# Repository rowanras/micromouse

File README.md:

# micromouse2019
A micromouse for the IEEE micromouse competetion. It uses a custom board with an stm32f405, three time of flight distance sensors, two pololu geared motors w/ encoders, and a drv8848 motor controller.

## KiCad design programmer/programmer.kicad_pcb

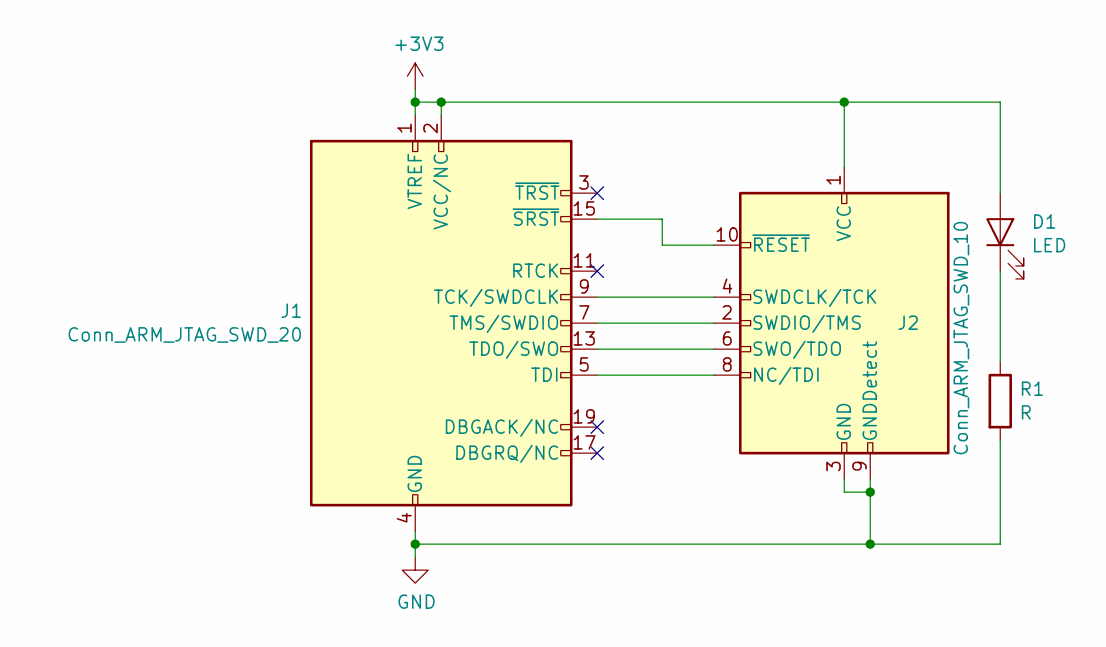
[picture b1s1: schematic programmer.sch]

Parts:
D1: LED; LED_0603_1608Metric
J1: Conn_ARM_JTAG_SWD_20; PinHeader_2x10_P2.54mm_Vertical
J2: Conn_ARM_JTAG_SWD_10; PinHeader_2x05_P1.27mm_Vertical_SMD
R1: R; R_0603_1608Metric

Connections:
+3V3: D1.2 (A), J1.1 (VTREF), J1.2 (VCC/NC), J2.1 (VCC)
GND: J1.4 (GND), J1.6 (GND), J1.8 (GND), J1.10 (GND), J1.12 (GND), J1.14 (GND), J1.16 (GND), J1.18 (GND), J1.20 (GND), J2.3 (GND), J2.5 (GND), J2.9 (GNDDetect), R1.2
unnamed: D1.1 (K), R1.1
unnamed: J1.5 (TDI), J2.8 (NC/TDI)
unnamed: J1.7 (TMS/SWDIO), J2.2 (SWDIO/TMS)
unnamed: J1.9 (TCK/SWDCLK), J2.4 (SWDCLK/TCK)
unnamed: J1.13 (TDO/SWO), J2.6 (SWO/TDO)
unnamed: J1.15 (~SRST~), J2.10 (~RESET~)

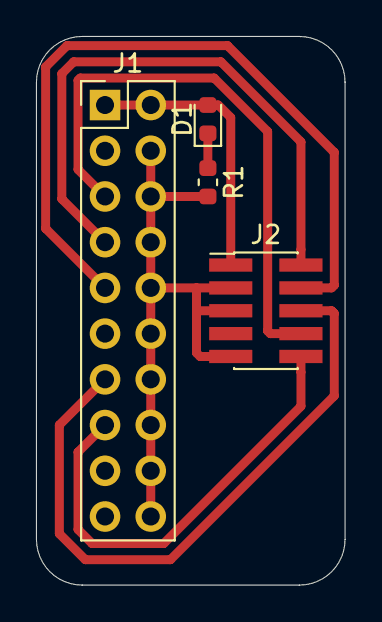
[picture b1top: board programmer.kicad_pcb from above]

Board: 2 copper layers, 17.1 x 30.5 mm, 4 parts (0 on the bottom side), 8 nets.

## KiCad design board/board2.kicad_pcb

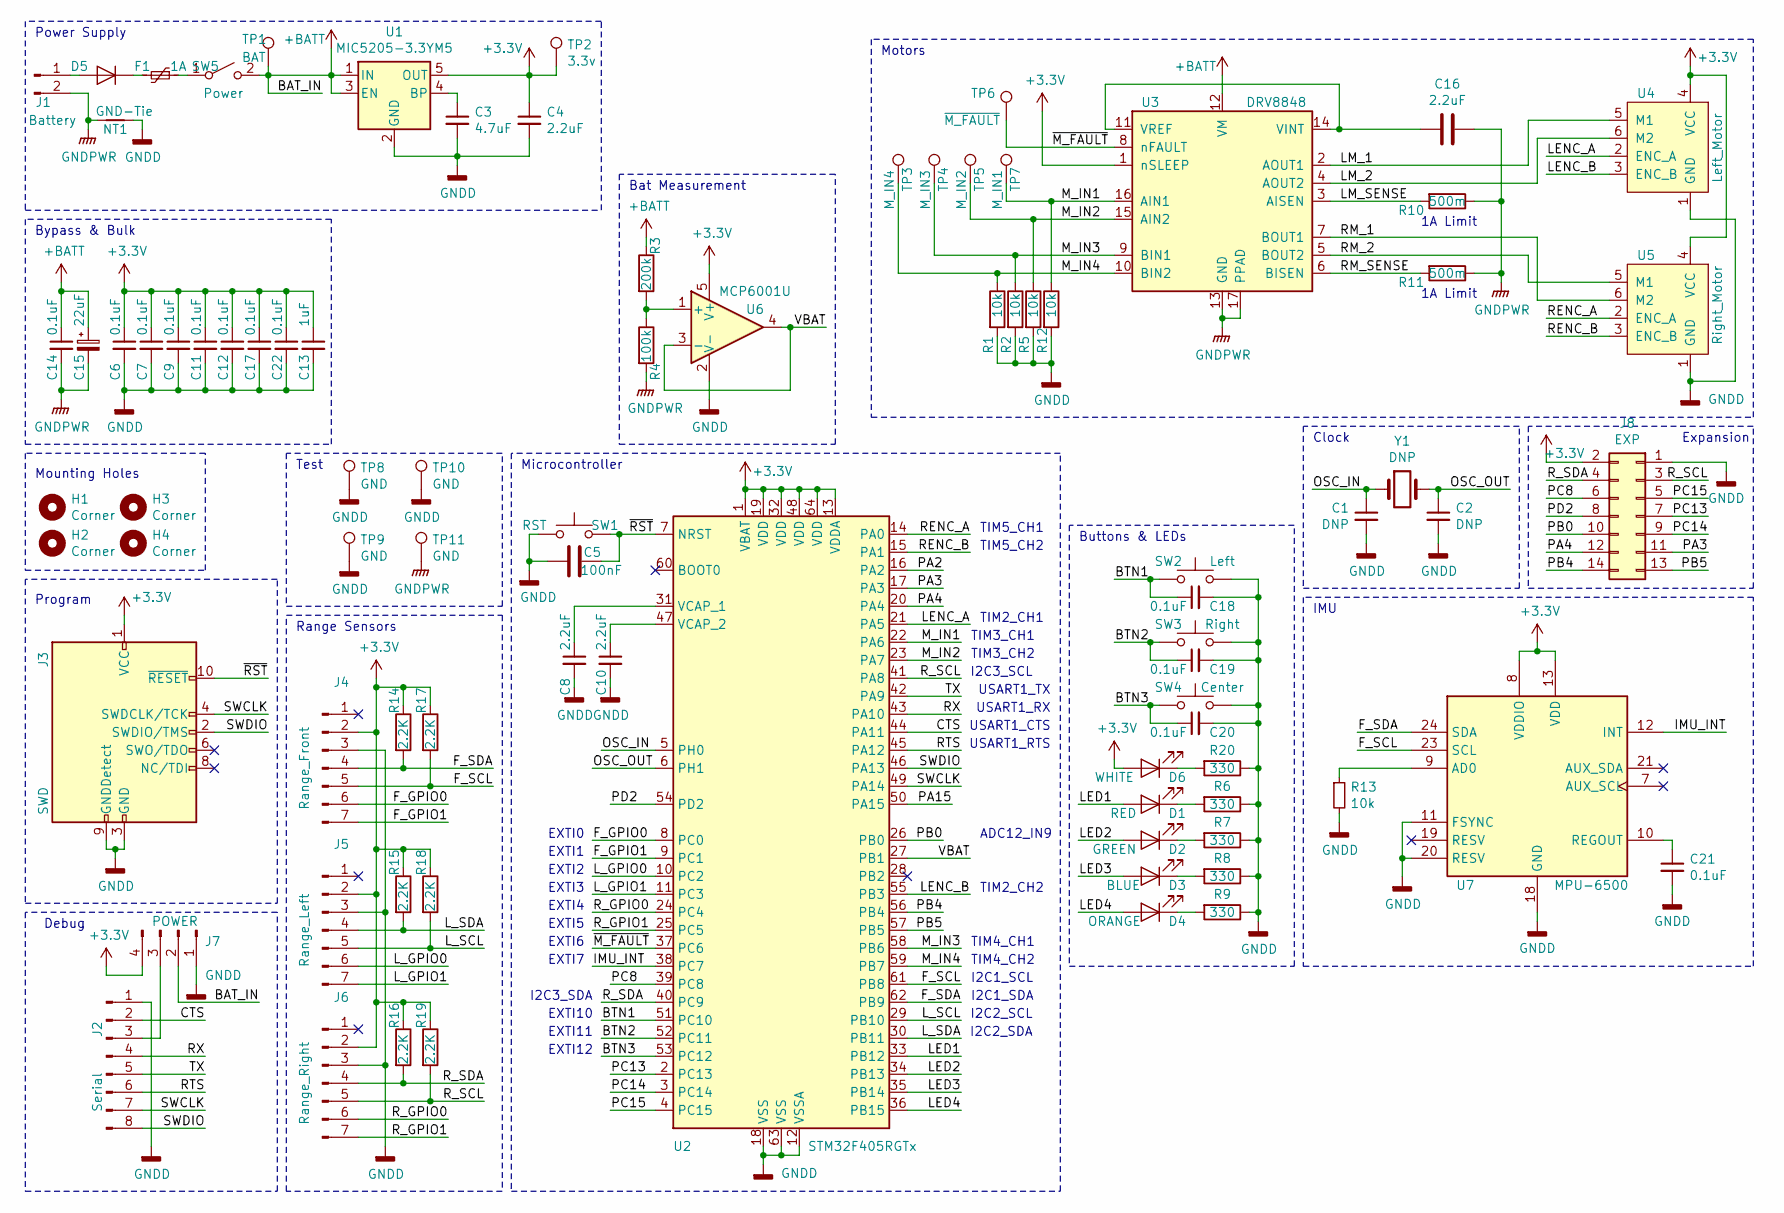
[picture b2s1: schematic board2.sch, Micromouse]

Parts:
C1, C2: DNP; C_0603_1608Metric
C3: 4.7uF; C_0603_1608Metric
C4, C8, C10, C16: 2.2uF; C_0603_1608Metric
C5: 100nF; C_0603_1608Metric
C6, C7, C9, C11, C12, C14, C17, C18, C19, C20, C21, C22: 0.1uF; C_0603_1608Metric
C13: 1uF; C_0603_1608Metric
C15: 22uF; CP_Elec_4x4.5
D1: RED; LED_0603_1608Metric
D2: GREEN; LED_0603_1608Metric
D3: BLUE; LED_0603_1608Metric
D4: ORANGE; LED_0603_1608Metric
D5: DB2441700L; SC-110A-2
D6: WHITE; LED_0603_1608Metric
F1: 1A; Littlefuse_154
H1, H2, H3, H4: Corner; MountingHole_2.2mm_M2
J1: Battery; PinHeader_1x02_P2.54mm_Horizontal
J2: Serial; PinHeader_1x08_P2.54mm_Vertical_SMD_Pin1Left
J3: SWD; PinHeader_2x05_P1.27mm_Vertical_SMD
J4: Range_Front; PinSocket_1x07_P2.54mm_Vertical
J5: Range_Left; PinSocket_1x07_P2.54mm_Vertical
J6: Range_Right; PinSocket_1x07_P2.54mm_Vertical
J7: POWER; PinHeader_1x04_P2.54mm_Vertical_SMD_Pin1Left
J8: EXP; PinHeader_2x07_P2.00mm_Vertical_SMD
NT1: GND-Tie; NetTie-2_SMD_Pad0.5mm
R1, R2, R5, R12, R13: 10k; R_0603_1608Metric
R3: 200k; R_0603_1608Metric
R4: 100k; R_0603_1608Metric
R6, R7, R8, R9, R20: 330; R_0603_1608Metric
R10, R11: 500m; R_1210_3225Metric
R14, R15, R16, R17, R18, R19: 2.2K; R_0603_1608Metric
SW1: RST; SW_SPST_PTS810
SW2: Left; SW_SPST_PTS810
SW3: Right; SW_SPST_PTS810
SW4: Center; SW_SPST_PTS810
SW5: Power; PinHeader_2x01_P2.54mm_Vertical_SMD
TP1: BAT; TestPoint_Pad_1.8x1.0mm
TP2: 3.3v; TestPoint_Pad_1.8x1.0mm
TP3: M_IN4; TestPoint_Pad_1.8x1.0mm
TP4: M_IN3; TestPoint_Pad_1.8x1.0mm
TP5: M_IN2; TestPoint_Pad_1.8x1.0mm
TP6: ~M_FAULT; TestPoint_Pad_1.8x1.0mm
TP7: M_IN1; TestPoint_Pad_1.8x1.0mm
TP8, TP9, TP10, TP11: GND; TestPoint_Pad_1.8x1.0mm
U1: MIC5205-3.3YM5; SOT-23-5
U2: STM32F405RGTx; LQFP-64_10x10mm_P0.5mm
U3: DRV8848; TSSOP-16_4.4x5mm_P0.65mm
U4: Left_Motor; Molex_PicoBlade_53261-0671_1x06-1MP_P1.25mm_Horizontal
U5: Right_Motor; Molex_PicoBlade_53261-0671_1x06-1MP_P1.25mm_Horizontal
U6: MCP6001U; SOT-23-5
U7: MPU-6500; InvenSense_QFN-24_3x3mm_P0.4mm
Y1: DNP; Crystal_SMD_0603-2Pin_6.0x3.5mm

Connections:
+3V3: C4.1, C6.1, C7.1, C9.1, C11.1, C12.1, C13.1, C17.1, C22.1, D6.2 (A), J3.1 (VCC), J4.2, J5.2, J6.2, J7.4, J8.2, R14.1, R15.1, R16.1, R17.1, R18.1, R19.1, TP2.1, U1.5 (OUT), U2.1 (VBAT), U2.13 (VDDA), U2.19 (VDD), U2.32 (VDD), U2.48 (VDD), U2.64 (VDD), U3.1 (nSLEEP), U4.4 (VCC), U5.4 (VCC), U6.5 (V+), U7.8 (VDDIO), U7.13 (VDD)
+BATT: C14.1, C15.1, J7.2, R3.1, SW5.2 (B), TP1.1, U1.1 (IN), U1.3 (EN), U3.12 (VM)
/BTN1: C18.1, SW2.1, U2.51 (PC10)
/BTN2: C19.1, SW3.1, U2.52 (PC11)
/BTN3: C20.1, SW4.1, U2.53 (PC12)
/CTS: J2.2, U2.44 (PA11)
/F_GPIO0: J4.6, U2.8 (PC0)
/F_GPIO1: J4.7, U2.9 (PC1)
/F_SCL: J4.5, R17.2, U2.61 (PB8), U7.23 (SCL)
/F_SDA: J4.4, R14.2, U2.62 (PB9), U7.24 (SDA)
/IMU_INT: U2.38 (PC7), U7.12 (INT)
/LED1: D1.2 (A), U2.33 (PB12)
/LED2: D2.2 (A), U2.34 (PB13)
/LED3: D3.2 (A), U2.35 (PB14)
/LED4: D4.2 (A), U2.36 (PB15)
/LENC_A: U2.21 (PA5), U4.2 (ENC_A)
/LENC_B: U2.55 (PB3), U4.3 (ENC_B)
/LM_1: U3.2 (AOUT1), U4.5 (M1)
/LM_2: U3.4 (AOUT2), U4.6 (M2)
/LM_SENSE: R10.2, U3.3 (AISEN)
/L_GPIO0: J5.6, U2.10 (PC2)
/L_GPIO1: J5.7, U2.11 (PC3)
/L_SCL: J5.5, R18.2, U2.29 (PB10)
/L_SDA: J5.4, R15.2, U2.30 (PB11)
/M_IN1: R12.1, TP7.1, U2.22 (PA6), U3.16 (AIN1)
/M_IN2: R5.1, TP5.1, U2.23 (PA7), U3.15 (AIN2)
/M_IN3: R2.1, TP4.1, U2.58 (PB6), U3.9 (BIN1)
/M_IN4: R1.1, TP3.1, U2.59 (PB7), U3.10 (BIN2)
/OSC_IN: C1.1, U2.5 (PH0), Y1.1
/OSC_OUT: C2.1, U2.6 (PH1), Y1.2
/PA3: J8.11, U2.17 (PA3)
/PA4: J8.12, U2.20 (PA4)
/PB0: J8.10, U2.26 (PB0)
/PB4: J8.14, U2.56 (PB4)
/PB5: J8.13, U2.57 (PB5)
/PC8: J8.6, U2.39 (PC8)
/PC13: J8.7, U2.2 (PC13)
/PC14: J8.9, U2.3 (PC14)
/PC15: J8.5, U2.4 (PC15)
/PD2: J8.8, U2.54 (PD2)
/RENC_A: U2.14 (PA0), U5.2 (ENC_A)
/RENC_B: U2.15 (PA1), U5.3 (ENC_B)
/RM_1: U3.7 (BOUT1), U5.6 (M2)
/RM_2: U3.5 (BOUT2), U5.5 (M1)
/RM_SENSE: R11.2, U3.6 (BISEN)
/RTS: J2.6, U2.45 (PA12)
/RX: J2.4, U2.43 (PA10)
/R_GPIO0: J6.6, U2.24 (PC4)
/R_GPIO1: J6.7, U2.25 (PC5)
/R_SCL: J6.5, J8.3, R19.2, U2.41 (PA8)
/R_SDA: J6.4, J8.4, R16.2, U2.40 (PC9)
/SWCLK: J2.7, J3.4 (SWDCLK/TCK), U2.49 (PA14)
/SWDIO: J2.8, J3.2 (SWDIO/TMS), U2.46 (PA13)
/TX: J2.5, U2.42 (PA9)
/VBAT: U2.27 (PB1), U6.3 (-), U6.4
/~M_FAULT: TP6.1, U2.37 (PC6), U3.8 (nFAULT)
/~RST: C5.1, J3.10 (~RESET~), SW1.2, U2.7 (NRST)
GNDD: C1.2, C2.2, C3.2, C4.2, C5.2, C6.2, C7.2, C8.2, C9.2, C10.2, C11.2, C12.2, C13.2, C17.2, C18.2, C19.2, C20.2, C21.2, C22.2, J2.1, J3.3 (GND), J3.5 (GND), J3.9 (GNDDetect), J4.3, J5.3, J6.3, J7.1, J8.1, NT1.2, R1.2, R2.2, R5.2, R6.1, R7.1, R8.1, R9.1, R12.2, R13.2, R20.1, SW1.1, SW2.2, SW3.2, SW4.2, TP8.1, TP9.1, TP10.1, U1.2 (GND), U2.12 (VSSA), U2.18 (VSS), U2.63 (VSS), U4.1 (GND), U5.1 (GND), U6.2 (V-), U7.11 (FSYNC), U7.18 (GND), U7.20 (RESV)
GNDPWR: C14.2, C15.2, C16.1, J1.2, NT1.1, R4.2, R10.1, R11.1, TP11.1, U3.13 (GND), U3.17 (PPAD)
unnamed: C3.1, U1.4 (BP)
unnamed: C8.1, U2.31 (VCAP_1)
unnamed: C10.1, U2.47 (VCAP_2)
unnamed: C16.2, U3.11 (VREF), U3.14 (VINT)
unnamed: C21.1, U7.10 (REGOUT)
unnamed: D1.1 (K), R6.2
unnamed: D2.1 (K), R7.2
unnamed: D3.1 (K), R8.2
unnamed: D4.1 (K), R9.2
unnamed: D5.1 (K), F1.2
unnamed: D5.2 (A), J1.1
unnamed: D6.1 (K), R20.2
unnamed: F1.1, SW5.1 (A)
unnamed: J2.3, J7.3
unnamed: R3.2, R4.1, U6.1 (+)
unnamed: R13.1, U7.9 (AD0)

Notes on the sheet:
TIM3_CH1
TIM3_CH2
TIM4_CH1
TIM4_CH2
TIM5_CH1
TIM5_CH2
TIM2_CH1
TIM2_CH2
I2C1_SCL
I2C1_SDA
I2C2_SCL
I2C2_SDA
I2C3_SCL
I2C3_SDA
EXTI0
EXTI1
EXTI2
EXTI3
EXTI4
EXTI5
EXTI6
USART1_TX
USART1_RX
USART1_CTS
USART1_RTS
EXTI10
EXTI11
EXTI12
ADC12_IN9
EXTI7
Range Sensors
IMU
Microcontroller
Buttons & LEDs
Expansion
Clock
Program
Debug
Test
Power Supply

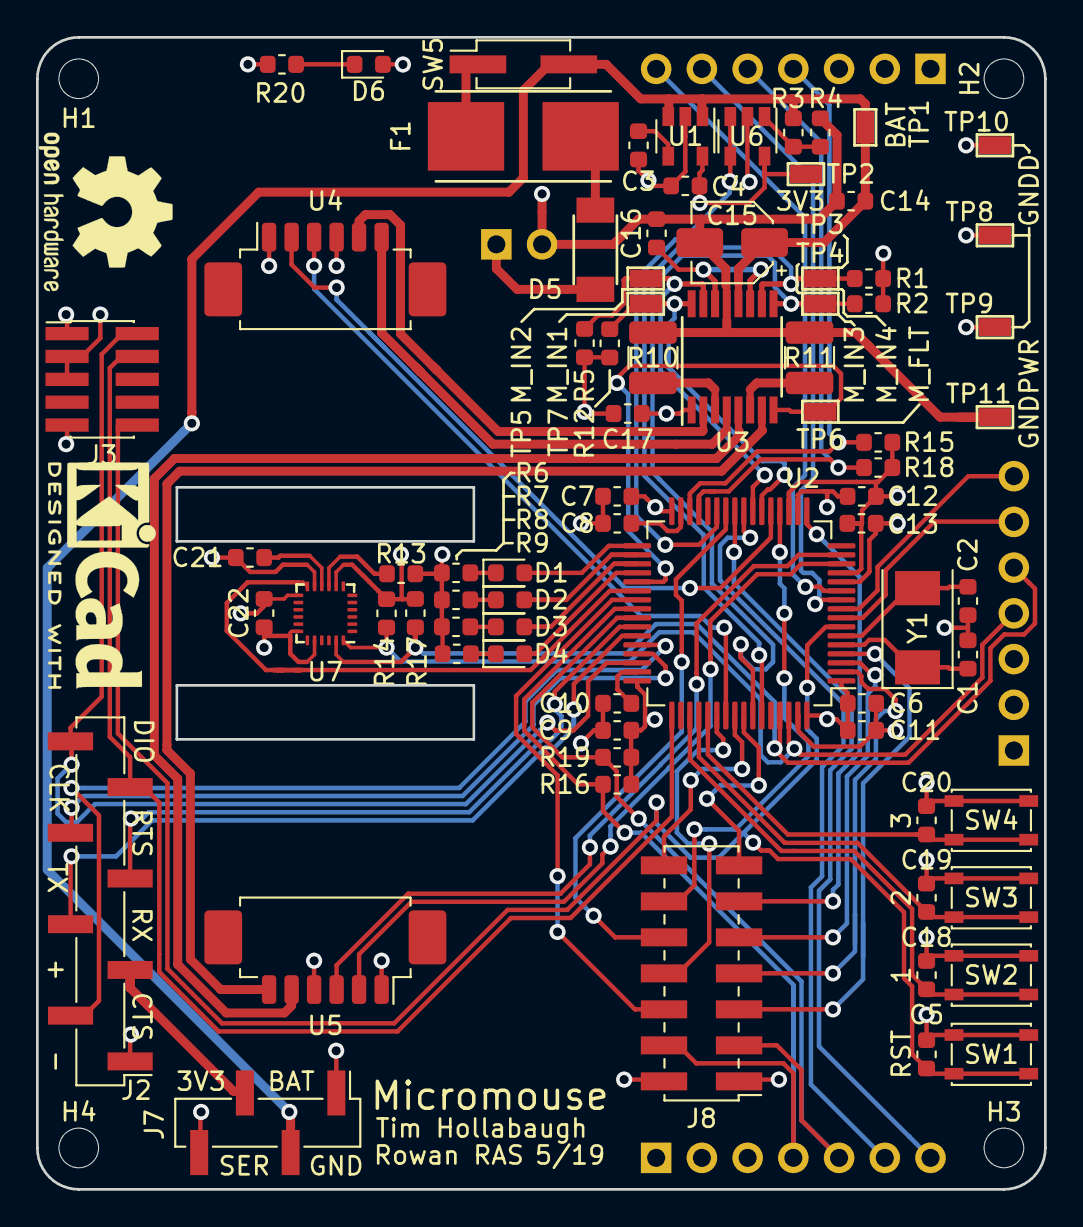
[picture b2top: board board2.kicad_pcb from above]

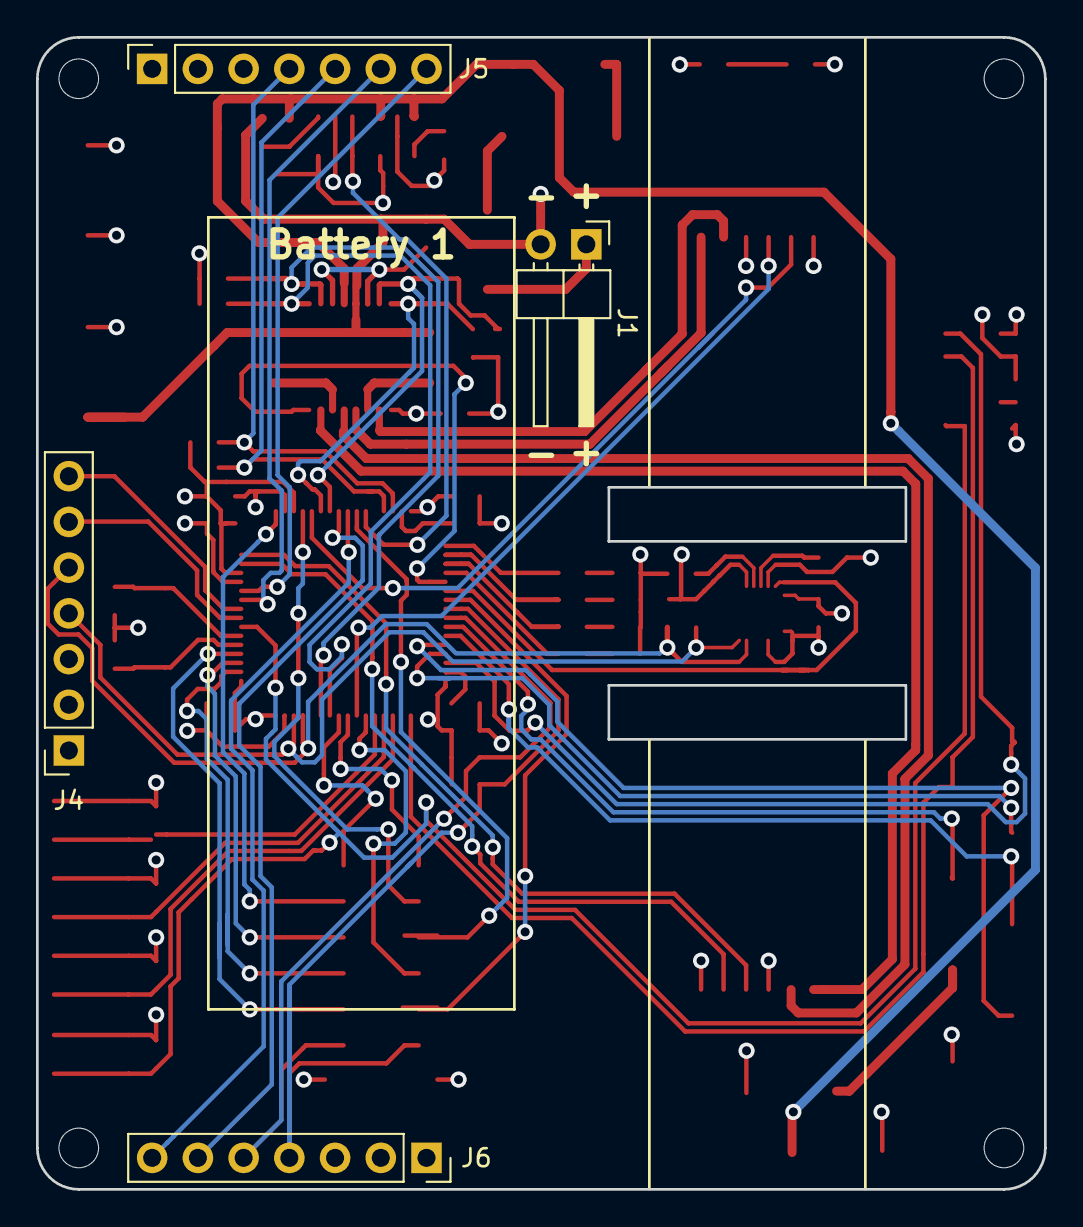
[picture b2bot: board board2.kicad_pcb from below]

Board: 4 copper layers, 56.0 x 64.0 mm, 86 parts (4 on the bottom side), 75 nets.

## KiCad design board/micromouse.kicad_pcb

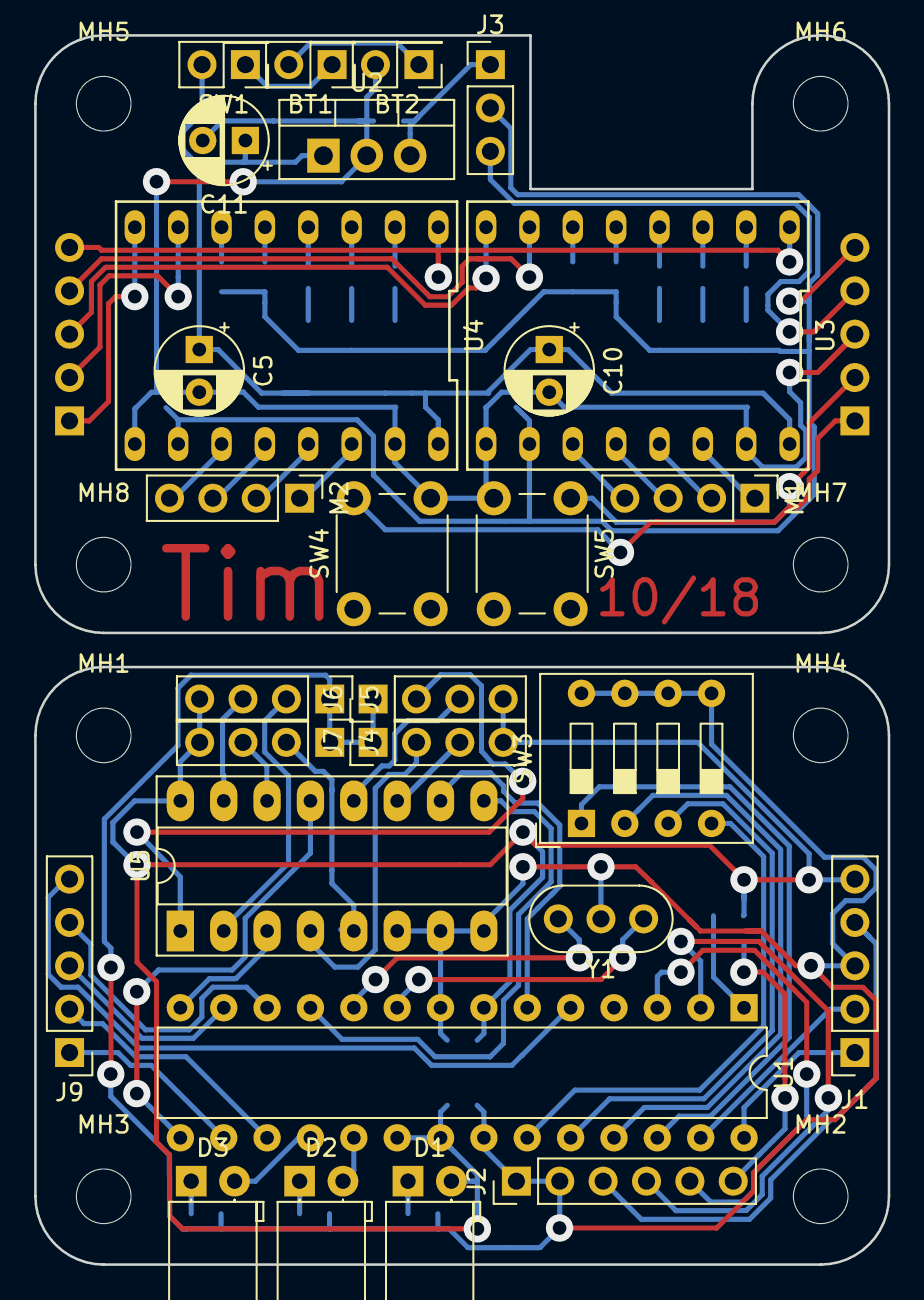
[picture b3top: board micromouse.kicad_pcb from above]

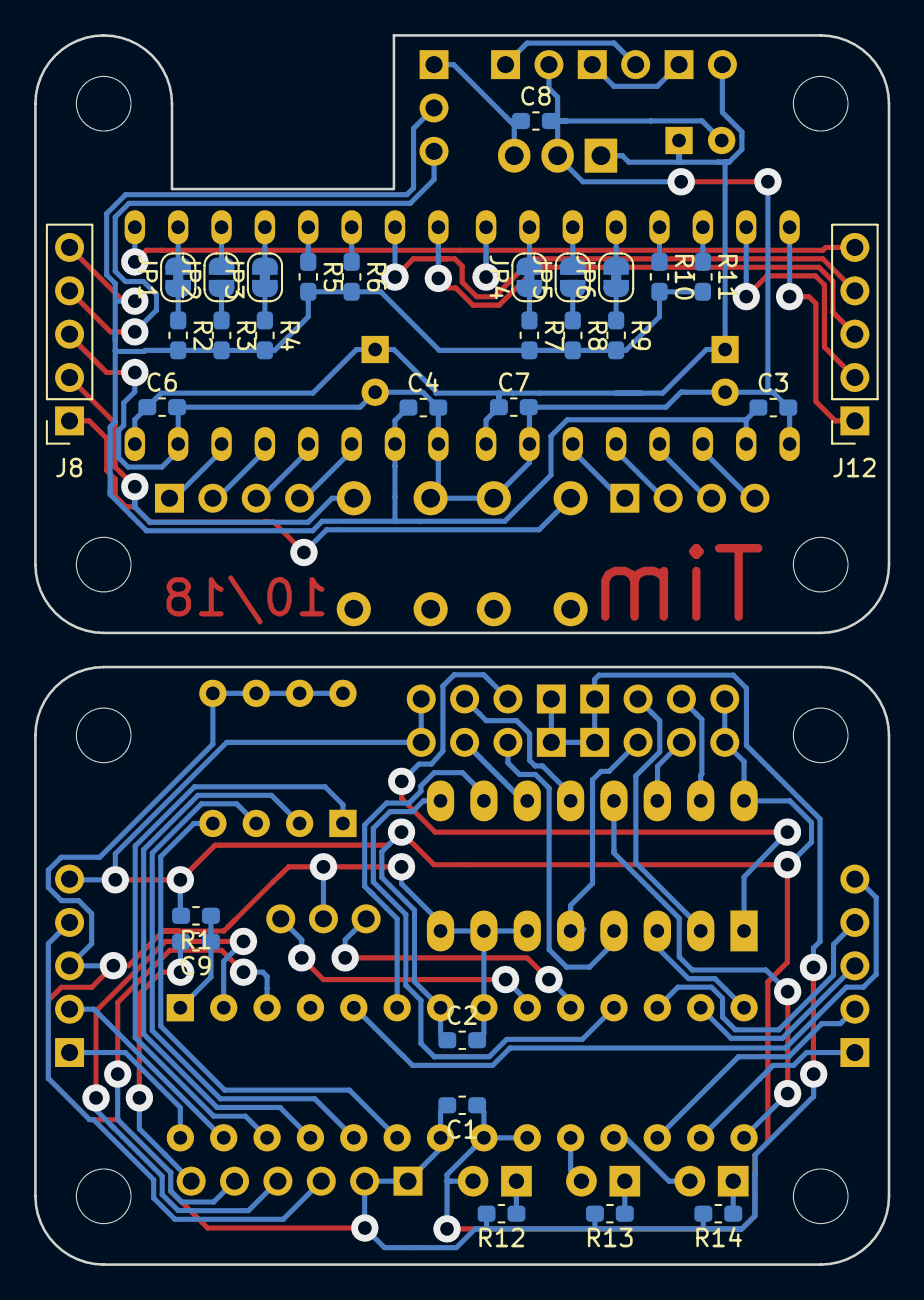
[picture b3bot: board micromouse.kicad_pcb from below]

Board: 2 copper layers, 50.0 x 72.0 mm, 66 parts (30 on the bottom side), 75 nets.

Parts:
BT1, BT2: 3x AA; PinHeader_2x01_P2.54mm_Vertical
C1, C2, C3, C4, C6, C7, C9: 0.1uF; C_0603_1608Metric_Pad1.05x0.95mm_HandSolder
C5: 0.33uf; CP_Radial_D5.0mm_P2.50mm
C8: 0.1uf; C_0603_1608Metric_Pad1.05x0.95mm_HandSolder
C10, C11: CP; CP_Radial_D5.0mm_P2.50mm
D1, D2, D3: LED; LED_D5.0mm_Horizontal_O1.27mm_Z3.0mm
J1: PowerBtnLower; PinSocket_1x05_P2.54mm_Vertical
J2: SERIAL; PinHeader_1x06_P2.54mm_Vertical
J3: PWR_SEL; PinHeader_1x03_P2.54mm_Vertical
J4: Front Sense; PinHeader_1x04_P2.54mm_Vertical
J5: Left Sense; PinHeader_1x04_P2.54mm_Vertical
J6: Right Sense; PinHeader_1x04_P2.54mm_Vertical
J7: Back Sense; PinHeader_1x04_P2.54mm_Vertical
J8: PowerBtnUpper; PinSocket_1x05_P2.54mm_Vertical
J9: MotorsLower; PinHeader_1x05_P2.54mm_Vertical
J12: MotorsUpper; PinSocket_1x05_P2.54mm_Vertical
JP1, JP4: MS1; SolderJumper-2_P1.3mm_Bridged_RoundedPad1.0x1.5mm
JP2, JP5: MS2; SolderJumper-2_P1.3mm_Open_RoundedPad1.0x1.5mm
JP3, JP6: MS3; SolderJumper-2_P1.3mm_Bridged_RoundedPad1.0x1.5mm
M1: Left Motor; PinHeader_1x04_P2.54mm_Vertical
M2: Right Motor; PinHeader_1x04_P2.54mm_Vertical
MH1, MH2, MH3, MH4, MH5, MH6, MH7, MH8: MountingHole; MountingHole_3.2mm_M3
R1, R2, R3, R4, R5, R6, R7, R8, R9, R10, R11: 1K; R_0603_1608Metric_Pad1.05x0.95mm_HandSolder
R12, R13, R14: 470; R_0603_1608Metric_Pad1.05x0.95mm_HandSolder
SW1: SW_SPST; PinHeader_2x01_P2.54mm_Vertical
SW3: SW_DIP_x04; SW_DIP_SPSTx04_Slide_9.78x12.34mm_W7.62mm_P2.54mm
SW4, SW5: SW_Push; SW_PUSH_6mm
U1: ATmega328P-PU; DIP-28_W7.62mm
U2: L7805; TO-220-3_Vertical
U3, U4: drv8825; DIP-16_500_ELL
U5: CD4052B; DIP-16_W7.62mm_Socket_LongPads
Y1: 16MHz; Resonator-3Pin_W8.0mm_H3.5mm

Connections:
+5V: C3.1, C4.1, J3.2, J8.5, R2.2, R3.2, R4.2, R5.2, R6.2, R7.2, R8.2, R9.2, R10.2, R11.2, U3.10, U4.10
+5VD: C1.1, C2.1, D1.2, J1.5, J4.4, J5.4, J6.4, J7.4, R1.2, U1.7, U1.20, U1.21, U5.16
+BATT: C5.1, C6.1, C7.1, C10.1, C11.1, SW1.2, U2.1, U3.16, U4.16
/BACK_ECHO: J7.2, U5.4
/BACK_TRIG: J7.3, U5.11
/BTN1: J1.1, U1.28
/BTN1_T: J8.1, SW4.1
/BTN2: J1.2, U1.27
/BTN2_T: J8.2, SW5.1
/FRONT_ECHO: J4.2, U5.5
/FRONT_TRIG: J4.3, U5.14
/LED1: D2.2, U1.19
/LED2: D3.2, U1.18
/LEFT_DIR: J9.3, U1.13
/LEFT_DIR_T: J12.3, U3.8
/LEFT_ECHO: J5.2, U5.2
/LEFT_STEP: J9.4, U1.12
/LEFT_STEP_T: J12.4, U3.7
/LEFT_TRIG: J5.3, U5.15
/M_ENABLE: J9.5, U1.5
/M_ENABLE_T: J12.5, U3.1, U4.1
/RIGHT_DIR: J9.1, U1.16
/RIGHT_DIR_T: J12.1, U4.8
/RIGHT_ECHO: J6.2, U5.1
/RIGHT_STEP: J9.2, U1.17
/RIGHT_STEP_T: J12.2, U4.7
/RIGHT_TRIG: J6.3, U5.12
/RST: C9.1, R1.1, U1.1
/RX: J2.4, U1.2
/SENSE_ECHO: U1.14, U5.3
/SENSE_SEL_0: U1.6, U5.10
/SENSE_SEL_1: U1.11, U5.9
/SENSE_TRIG: U1.15, U5.13
/TX: J2.5, U1.3
/USB_5V: J1.4, J2.3
/USB_5V_T: J3.3, J8.4
/XTAL1: U1.9, Y1.1
/XTAL2: U1.10, Y1.3
GND: BT2.2, C3.2, C4.2, C5.2, C6.2, C7.2, C8.2, C10.2, C11.2, J8.3, SW4.2, SW5.2, U2.2, U3.9, U3.15, U4.9, U4.15
GNDD: C1.2, C2.2, J1.3, J2.1, J2.2, J4.1, J5.1, J6.1, J7.1, R12.2, R13.2, R14.2, SW3.5, SW3.6, SW3.7, SW3.8, U1.8, U1.22, U5.6, U5.7, U5.8, Y1.2
unnamed: BT1.1, SW1.1
unnamed: BT1.2, BT2.1
unnamed: C8.1, J3.1, U2.3
unnamed: C9.2, J2.6
unnamed: D1.1, R12.1
unnamed: D2.1, R13.1
unnamed: D3.1, R14.1
unnamed: JP1.1, R2.1
unnamed: JP1.2, U3.2
unnamed: JP2.1, R3.1
unnamed: JP2.2, U3.3
unnamed: JP3.1, R4.1
unnamed: JP3.2, U3.4
unnamed: JP4.1, R7.1
unnamed: JP4.2, U4.2
unnamed: JP5.1, R8.1
unnamed: JP5.2, U4.3
unnamed: JP6.1, R9.1
unnamed: JP6.2, U4.4
unnamed: M1.1, U3.14
unnamed: M1.2, U3.13
unnamed: M1.3, U3.12
unnamed: M1.4, U3.11
unnamed: M2.1, U4.14
unnamed: M2.2, U4.13
unnamed: M2.3, U4.12
unnamed: M2.4, U4.11
unnamed: R5.1, U3.5
unnamed: R6.1, U3.6
unnamed: R10.1, U4.5
unnamed: R11.1, U4.6
unnamed: SW3.1, U1.26
unnamed: SW3.2, U1.25
unnamed: SW3.3, U1.24
unnamed: SW3.4, U1.23

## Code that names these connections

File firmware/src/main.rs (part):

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    let gpiob = p.GPIOB.split();
    let gpioc = p.GPIOC.split();

    let mut red_led = gpiob.pb12.into_push_pull_output();
    let mut green_led = gpiob.pb13.into_push_pull_output();
    let mut blue_led = gpiob.pb14.into_push_pull_output();
    let mut orange_led = gpiob.pb15.into_push_pull_output();

    let left_button = gpioc.pc10.into_pull_up_input();
    let middle_button = gpioc.pc11.into_pull_up_input();
    let right_button = gpioc.pc12.into_pull_up_input();

    orange_led.set_high();
    blue_led.set_low();
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    writeln!(uart, "Initializing").ignore();

    let mut front_distance = {
        let scl = gpiob.pb8.into_open_drain_output().into_alternate_af4();
        let sda = gpiob.pb9.into_open_drain_output().into_alternate_af4();

        let mut gpio0 = gpioc.pc0.into_open_drain_output();
        gpio0.set_high();

        let mut gpio1 = gpioc.pc1.into_open_drain_output();
        gpio1.set_high();

        let i2c =
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    blue_led.set_high();

    let mut left_distance = {
        let scl = gpiob.pb10.into_open_drain_output().into_alternate_af4();
        let sda = gpiob.pb11.into_open_drain_output().into_alternate_af4();

        let mut gpio0 = gpioc.pc2.into_open_drain_output();
        gpio0.set_high();

        let mut gpio1 = gpioc.pc3.into_open_drain_output();
        gpio1.set_high();

        let i2c =
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    blue_led.set_high();

    let mut right_distance = {
        let scl = gpioa.pa8.into_open_drain_output().into_alternate_af4();
        let sda = gpioc.pc9.into_open_drain_output().into_alternate_af4();

        let mut gpio0 = gpioc.pc4.into_open_drain_output();
        gpio0.set_high();

        let mut gpio1 = gpioc.pc5.into_open_drain_output();
        gpio1.set_high();

        let i2c =
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
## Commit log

2018-09-15 board: initial commit
2018-09-15 firmware: init code and add stepper drivers
2018-09-21 finished board design
2018-09-21 added firmware gitignore
2018-09-21 added spreadsheet of timer configs for steppers
2018-10-09 Finished board layout
2018-10-09 UART transmit and initial ultrasonic attempt
2018-10-09 Add cad models of some parts
2018-10-23 Finish small board
2018-10-23 Neaten some traces
2018-12-04 One distaance sensor works
2018-12-04 Final 2-board design
2018-12-04 Add stl files for body
2018-12-04 Ignore cquery cache
2018-12-08 distance works, steppers going by steps
2018-12-08 set stepper motors with number of steps
    removes timing per step, since it used too much ram
2018-12-14 UART parsing, move by steps
2018-12-14 Calibrate steps per mm and steps per deg
2019-02-24 Created drawings for presentation
2019-02-24 Smaller boards to fit better
2019-02-24 Complete board redo
    Now uses stm32f405, dc motors + encoders, laser distance sensors
2019-02-24 Starting new firmware for new board
    Currently supports:
    - LEDs
    - PWM control of left motor
    - UART tx char
2019-02-24 Remove unused cmake files
2019-02-24 Add step files of parts used
2019-02-24 Update readme with new board design
2019-02-26 Pull uart out and use an output buffer
2019-03-10 Make uart a struct and impl Write
2019-03-10 Add left encoder module
2019-03-10 Move motors to own module
2019-03-10 Motor trait
2019-03-10 Encoder trait
2019-03-11 Add right motor, time, better uart
2019-03-11 Add correct datasheet for motor driver
2019-03-15 Add pictures of the micromouse
2019-03-15 Add rustfmt config
2019-03-15 PID motor control
2019-03-15 Plotting script to help PID tuning
2019-03-17 Battery monitoring
2019-03-17 Plot battery values
2019-03-17 Label the adc channel for battery voltage
2019-03-17 Remove now unused plot.gnuplot
2019-03-17 Tuned PIDs for acceleration control
2019-03-20 Attempt motion planning.
    Has bugs and does not work too well
2019-03-30 control, motor, some distance
2019-04-03 Final attempt at manual i2c
2019-04-03 Update schematic with better labels
2019-04-03 Add files to plot a picture of part of the board
2019-04-03 Integrate in vl6180x module and use embedded_hal
2019-04-03 Reset the time timer when initializing
2019-04-03 All three distance sensors work
2019-04-03 Read distance sensors async
2019-04-03 Put distance sensors in bot
2019-04-03 Move BotConfig to own module
2019-04-04 Use distance sensors to drive straight and center
2019-04-04 Basic Plan layout
2019-04-05 Planner with random navigation
2019-04-05 Move navigation to Navigate trait
2019-04-05 Add stm32f4xx-hal as git repo
2019-04-05 Fix random navigate bug
2019-04-06 Buttons for start stop
2019-04-06 Start basic simulation
2019-04-06 Don't recenter after a move
2019-04-06 Adjust linear if a wall is seen
2019-04-06 Start with less random nav
2019-04-06 impl command for navigate
2019-04-06 More nav
2019-04-10 Final navigation module
2019-04-10 Simulation draws maze correctly
2019-04-10 Plot tweaks
2019-04-14 Better maze representation in simulator
2019-04-14 Start implementing update_cell for Maze
2019-05-09 Update for 3x3 maze demos
2019-05-09 Simulation renders maze
2019-05-09 Simulator simulates a mouse
2019-05-09 Add board svgs
2019-05-09 Board redesign
    - add IMU6500
    - only one battery
    - half the size
    - op amp buffer on battery monitor
    - 4 layer board
    - and more
2019-05-09 Add a bunch of mazes
    from https://github.com/micromouseonline/micromouse_maze_tool
2019-05-09 Move mouse logic into own struct
2019-05-09 Implement Counting Navigate
2019-05-11 Implement the rest of the algorithms
    and add script to run all of them
2019-05-11 Remove mazes that are not 16x16
2019-05-22 Final board layout
2019-06-26 Add dataflow diagram
2019-07-04 Make uart use interrupts, rustfmt
2019-07-06 Add micromouse_lib
    Will hold anything common between firmware and simulator
2019-07-06 Reports state over UART quickely
2019-07-06 Config in micromouse_lib
2019-07-06 simulator: Show mouse position and graph encoder
2019-07-07 simulator: switch to gtk
2019-07-07 simulation: switch to imgui
    should be a lot easier than gtk
2019-07-13 dynamically add plots
2019-07-13 Add history viewing
2019-07-13 firmware: allow setting motor speed over uart
2019-07-13 board: fix imu footprint
2019-07-13 micromouse_lib: Initial motion control
2019-07-13 all: add anaylysis of bytes sent over uart
2019-07-13 all: Add paths layout
2019-07-13 programmer: Add board used to connect to programmer
2019-07-13 simulation: specify where the state values are from
2019-07-16 Allow setting motor power
2019-07-18 micrmouse_lib: Define message type and to/from bytes
2019-07-18 firmware: Use micromouse_lib msgs to parse serial
2019-07-19 micromouse_lib: enumerate msg ids
2019-07-20 micromouse_lib: All config to f32
2019-07-20 micromouse_lib: Messages to choose what is logged
2019-07-20 firmware: use the latest parsers/generators for msgs
2019-07-21 micromouse_lib: add angular motion config
2019-07-21 micromouse_lib: add battery msg
2019-07-21 firmware: battery msgs, timeout
2019-07-21 simulation: New msg format
2019-07-21 update dataflow
2019-07-21 micromouse_lib: add mouse state
2019-07-22 all: Dynamic logging, velocity calc
2019-07-23 all: use cargo workspace and update dependencies
2019-07-23 all: Add distance msgs
2019-07-23 firmware: actually start distance ranging :)
2019-07-23 simulation: show distance values
2019-08-03 Add commands for targets, at
2019-08-03 simulation: uart waits for bluetooth to connect
2019-08-03 simulation: Don't use property trait
2019-08-03 simulator: Don't print every message
2019-08-04 Adds travis.yml
2019-08-04 Update rust version in travis
    Also add verbose options to cargo builds
2019-08-04 Removes rust param from .travis.yml
2019-08-04 better motion profile
2019-08-04 Change nightly to stable in .travis.yml
2019-09-28 Path follow, bluetooth board
